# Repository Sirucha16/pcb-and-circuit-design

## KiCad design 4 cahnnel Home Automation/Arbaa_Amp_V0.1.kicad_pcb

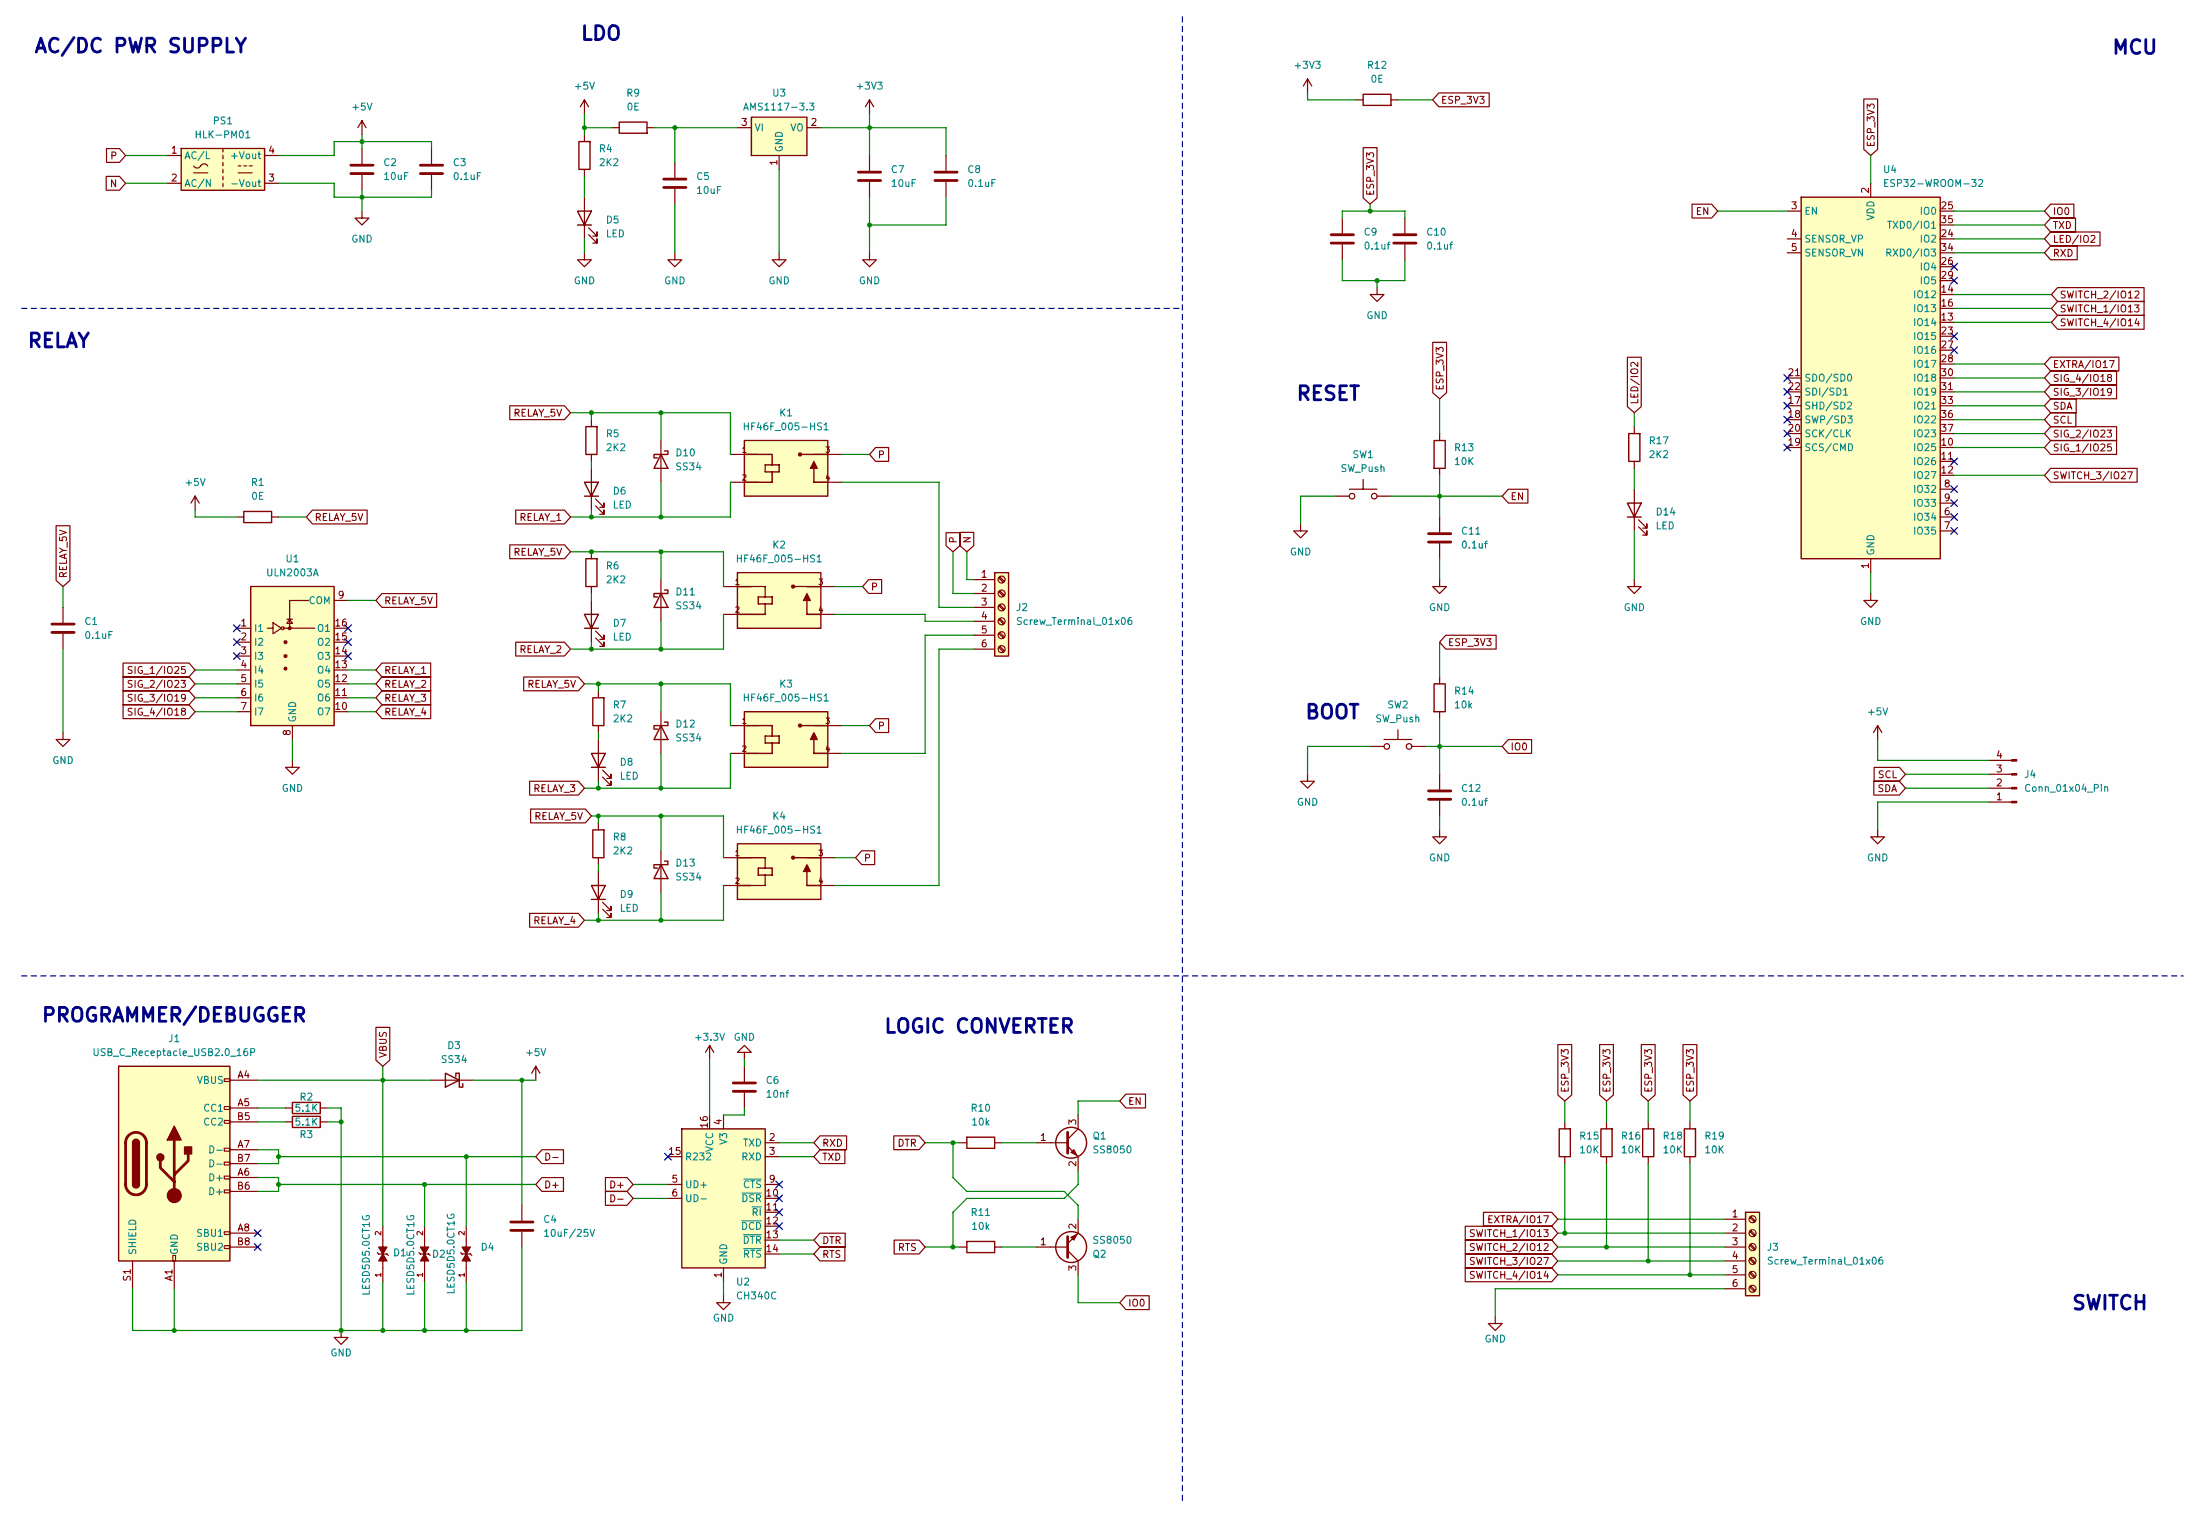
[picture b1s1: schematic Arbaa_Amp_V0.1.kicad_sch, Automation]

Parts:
C1, C3, C8: 0.1uF; C_0603_1608Metric
C2, C5, C7: 10uF; C_1206_3216Metric
C4: 10uF/25V; C_0603_1608Metric
C6: 10nf; C_1206_3216Metric
C9, C10, C11, C12: 0.1uf; C_0603_1608Metric
D1, D2, D4: LESD5D5.0CT1G; TVS_LESD5D5.0CT1G; PARTREV O
D3, D10, D11, D12, D13: SS34; D_SMA
D5, D6, D7, D8, D9, D14: LED; LED_0603_1608Metric
J1: USB_C_Receptacle_USB2.0_16P; USB_C_Receptacle_HCTL_HC-TYPE-C-16P-01A
J2, J3: Screw_Terminal_01x06; TerminalBlock_bornier-6_P5.08mm
J4: Conn_01x04_Pin; PinHeader_1x04_P2.54mm_Vertical
K1, K2, K3, K4: HF46F_005-HS1; RELAY_HF46F_005-HS1; PARTREV 1.00
PS1: HLK-PM01; Converter_ACDC_Hi-Link_HLK-PMxx
Q1, Q2: SS8050; SOT-23
R1, R9, R12: 0E; R_0603_1608Metric
R2, R3: 5.1K; R_0603_1608Metric
R4, R5, R6, R7, R8, R17: 2K2; R_0603_1608Metric
R10, R11, R14: 10k; R_0603_1608Metric
R13, R15, R16, R18, R19: 10K; R_0603_1608Metric
SW1, SW2: SW_Push; SW_Push_SPST_NO_Alps_SKRK
U1: ULN2003A; SOIC-16_3.9x9.9mm_P1.27mm
U2: CH340C; SOIC-16_3.9x9.9mm_P1.27mm
U3: AMS1117-3.3; SOT-223-3_TabPin2
U4: ESP32-WROOM-32

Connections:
+3.3V: U2.16 (VCC)
+3V3: C7.1, C8.1, R12.1, U3.2 (VO)
+5V: C2.1, C3.1, C4.1, D3.1 (K), J4.4, PS1.4 (+Vout), R1.1, R4.2, R9.1
D+: D2.2, J1.A6 (D+), J1.B6 (D+), U2.5 (UD+)
D-: D4.2, J1.A7 (D-), J1.B7 (D-), U2.6 (UD-)
DTR: Q2.2 (E), R10.2, U2.13 (~DTR)
EN: C11.1, Q1.3 (C), R13.2, SW1.2, U4.3 (EN)
ESP_3V3: C9.1, C10.1, R12.2, R13.1, R14.1, R15.2, R16.2, R18.2, R19.2, U4.2 (VDD)
EXTRA/IO17: J3.1, U4.28 (IO17)
GND: C1.2, C2.2, C3.2, C4.2, C5.2, C6.1, C7.2, C8.2, C9.2, C10.2, C11.2, C12.2, D1.1, D2.1, D4.1, D5.1 (K), D14.1 (K), J1.A1 (GND), J1.A12 (GND), J1.B1 (GND), J1.B12 (GND), J1.S1 (SHIELD), J3.6, J4.1, PS1.3 (-Vout), R2.2, R3.2, SW1.1, SW2.1, U1.8 (GND), U2.1 (GND), U3.1 (GND), U4.1 (GND), U4.15 (GND), U4.38 (GND), U4.39 (GND)
IO0: C12.1, Q2.3 (C), R14.2, SW2.2, U4.25 (IO0)
LED/IO2: R17.2, U4.24 (IO2)
N: J2.1, PS1.2 (AC/N)
unnamed: D5.2 (A), R4.1
unnamed: D6.2 (A), R5.1
unnamed: D7.2 (A), R6.1
unnamed: D8.2 (A), R7.1
unnamed: D9.2 (A), R8.1
unnamed: D14.2 (A), R17.1
unnamed: J1.A5 (CC1), R2.1
unnamed: J1.B5 (CC2), R3.1
unnamed: J2.3, K1.4
unnamed: J2.4, K2.4
unnamed: J2.5, K3.4
unnamed: J2.6, K4.4
unnamed: Q1.1 (B), R10.1
unnamed: Q2.1 (B), R11.1
unnamed: C6.2, U2.4 (V3)
unnamed: C5.1, R9.2, U3.3 (VI)
P: J2.2, K1.3, K2.3, K3.3, K4.3, PS1.1 (AC/L)
RELAY_1: D6.1 (K), D10.2 (A), K1.2, U1.13 (O4)
RELAY_2: D7.1 (K), D11.2 (A), K2.2, U1.12 (O5)
RELAY_3: D8.1 (K), D12.2 (A), K3.2, U1.11 (O6)
RELAY_4: D9.1 (K), D13.2 (A), K4.2, U1.10 (O7)
RELAY_5V: C1.1, D10.1 (K), D11.1 (K), D12.1 (K), D13.1 (K), K1.1, K2.1, K3.1, K4.1, R1.2, R5.2, R6.2, R7.2, R8.2, U1.9 (COM)
RTS: Q1.2 (E), R11.2, U2.14 (~RTS)
RXD: U2.2 (TXD), U4.34 (RXD0/IO3)
SCL: J4.3, U4.36 (IO22)
SDA: J4.2, U4.33 (IO21)
SIG_1/IO25: U1.4 (I4), U4.10 (IO25)
SIG_2/IO23: U1.5 (I5), U4.37 (IO23)
SIG_3/IO19: U1.6 (I6), U4.31 (IO19)
SIG_4/IO18: U1.7 (I7), U4.30 (IO18)
SWITCH_1/IO13: J3.2, R15.1, U4.16 (IO13)
SWITCH_2/IO12: J3.3, R16.1, U4.14 (IO12)
SWITCH_3/IO27: J3.4, R18.1, U4.12 (IO27)
SWITCH_4/IO14: J3.5, R19.1, U4.13 (IO14)
TXD: U2.3 (RXD), U4.35 (TXD0/IO1)
VBUS: D1.2, D3.2 (A), J1.A4 (VBUS), J1.A9 (VBUS), J1.B4 (VBUS), J1.B9 (VBUS)

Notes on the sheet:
SWITCH
MCU
PROGRAMMER/DEBUGGER
LOGIC CONVERTER
RESET
BOOT
LDO
RELAY
AC/DC PWR SUPPLY

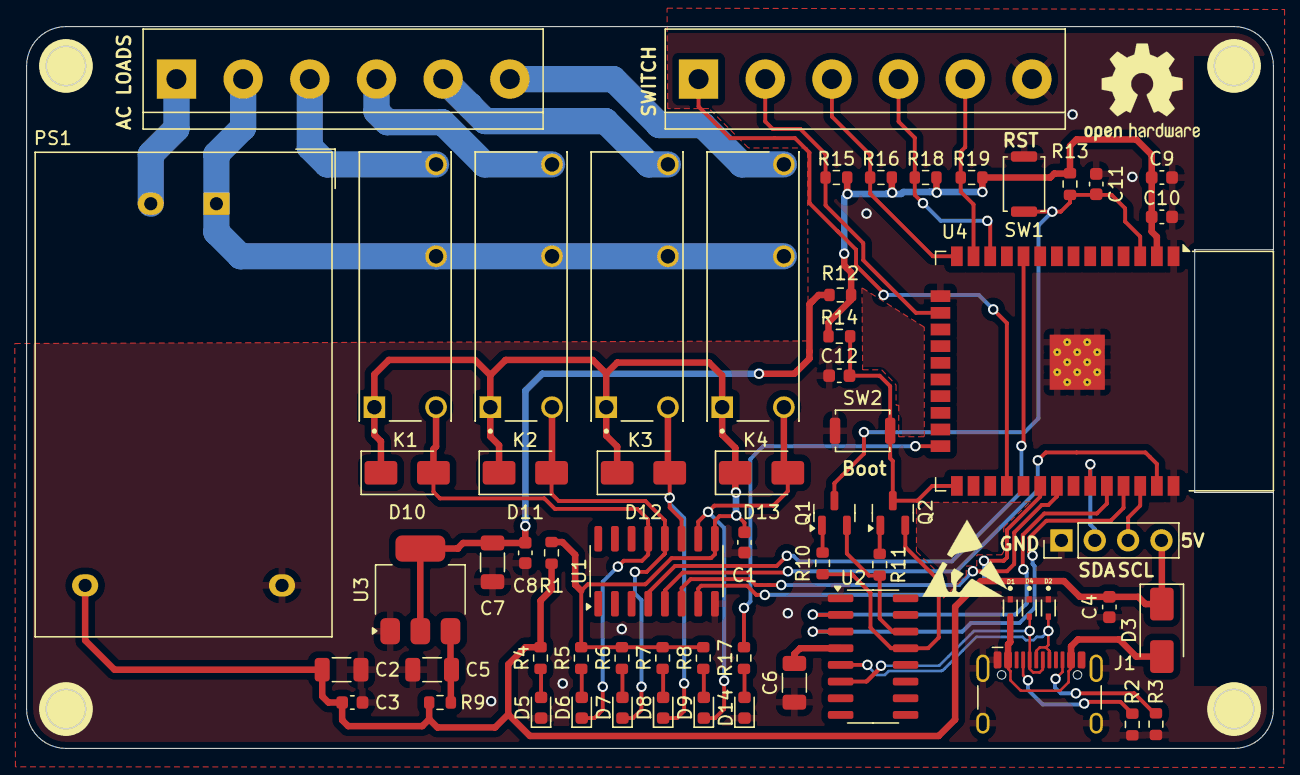
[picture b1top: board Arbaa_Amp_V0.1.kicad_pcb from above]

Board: 2 copper layers, 95.0 x 55.0 mm, 62 parts (0 on the bottom side), 48 nets.

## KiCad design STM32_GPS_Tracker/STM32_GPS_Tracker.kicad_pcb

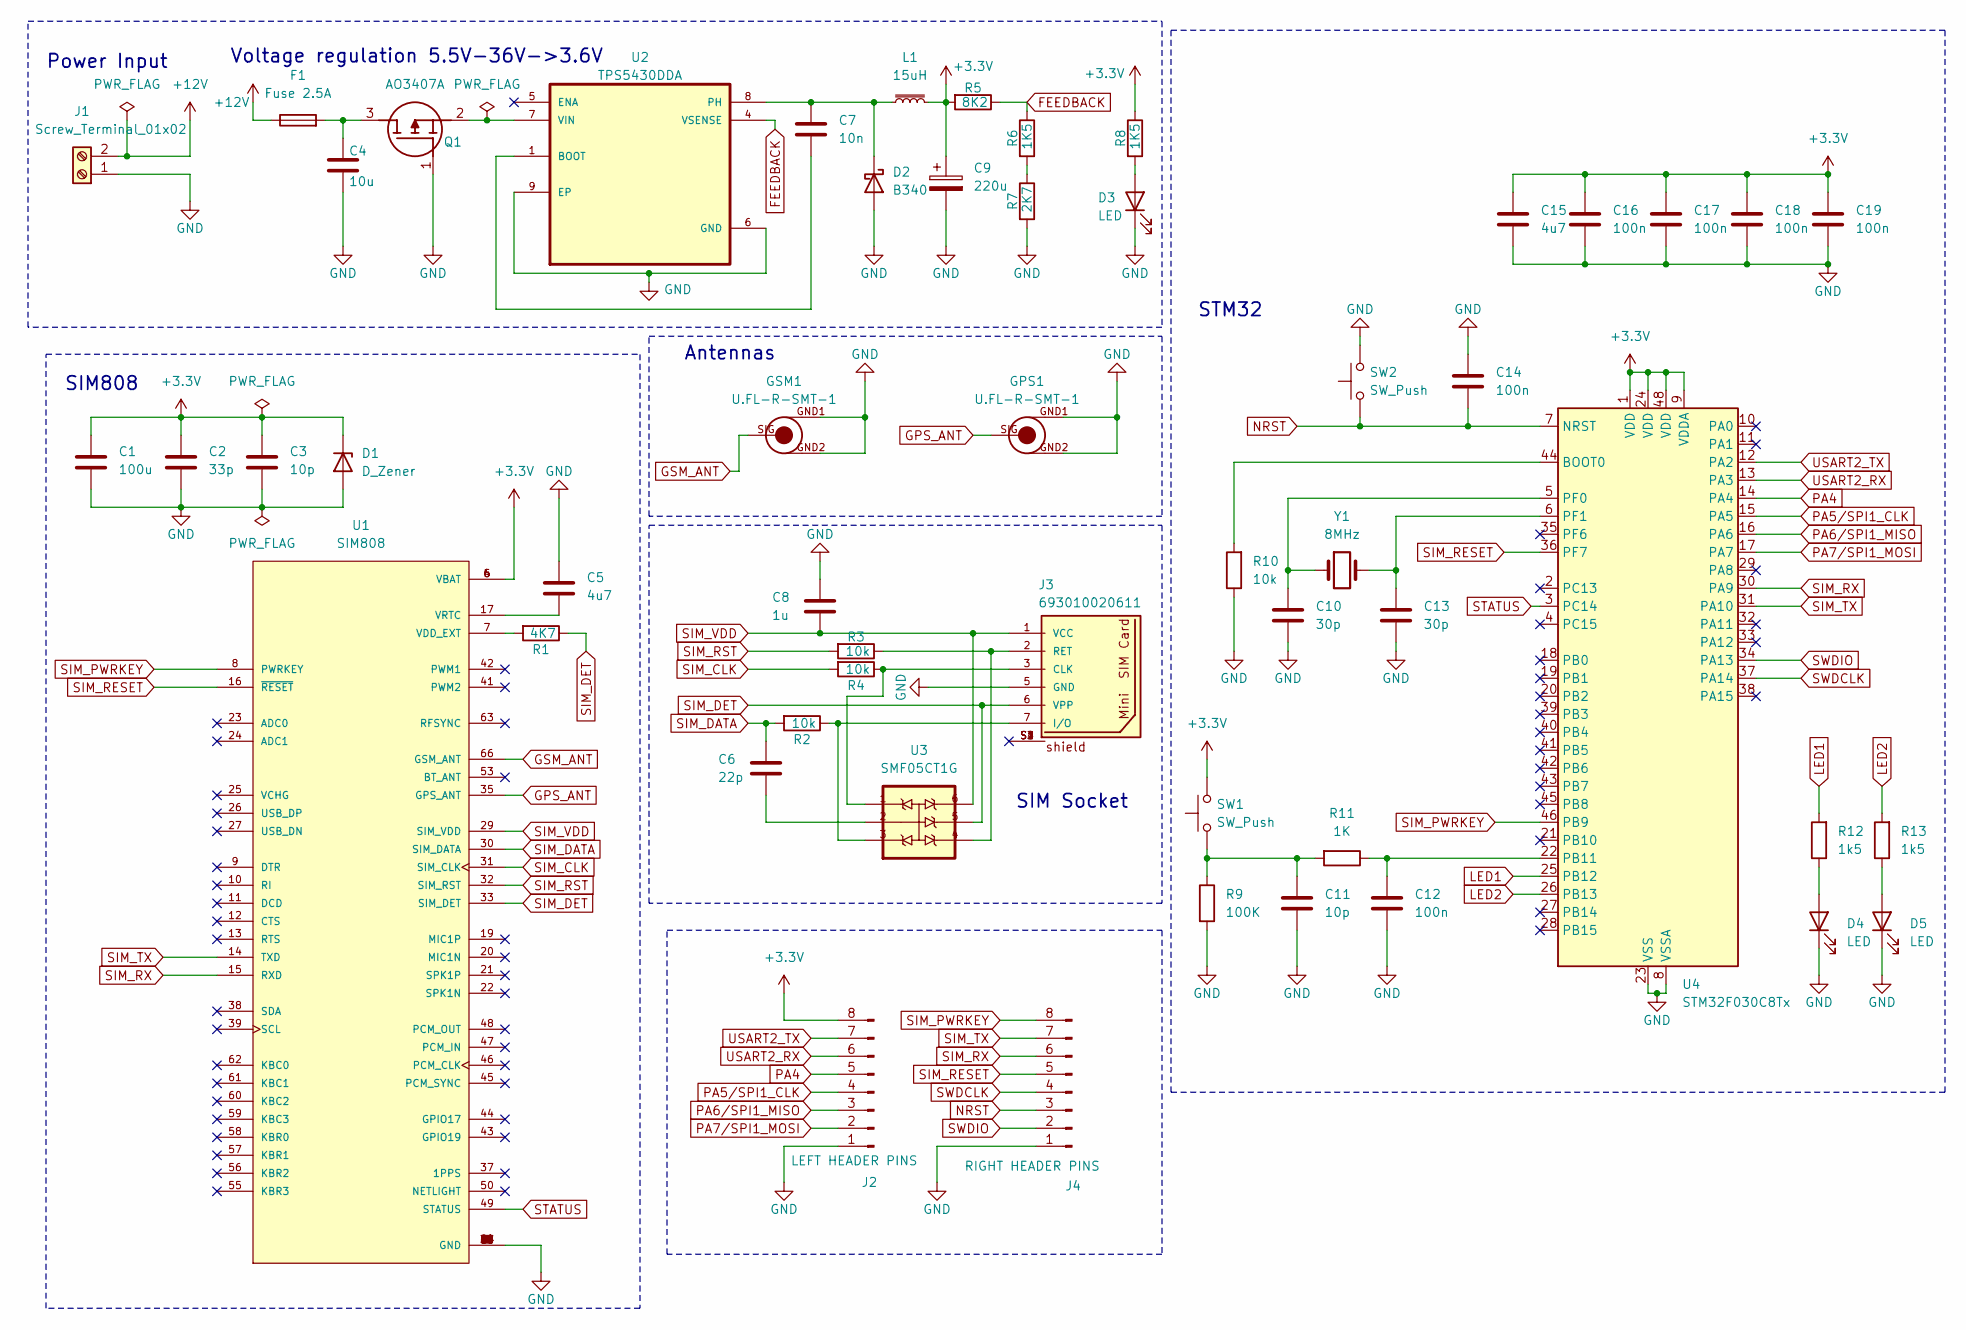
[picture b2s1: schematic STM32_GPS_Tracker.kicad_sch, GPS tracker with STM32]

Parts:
C1: 100u; C_1206_3216Metric
C2: 33p; C_0402_1005Metric
C3, C11: 10p; C_0402_1005Metric
C4: 10u; C_0805_2012Metric
C5, C15: 4u7; C_0201_0603Metric
C6: 22p; C_0402_1005Metric
C7: 10n; C_0201_0603Metric
C8: 1u; C_0402_1005Metric
C9: 220u; CP_EIA-7343-15_Kemet-W
C10, C13: 30p; C_0402_1005Metric
C12, C14, C16, C17, C18, C19: 100n; C_0402_1005Metric
D1: D_Zener; D_0805_2012Metric
D2: B340; D_SMC
D3, D4, D5: LED; LED_0603_1608Metric
F1: Fuse 2.5A; Fuse_0402_1005Metric
GPS1: U.FL-R-SMT-1
GSM1: U.FL-R-SMT-1
J1: Screw_Terminal_01x02; TerminalBlock_Phoenix_MKDS-1,5-2_1x02_P5.00mm_Horizontal
J2: LEFT HEADER PINS; PinHeader_1x08_P2.54mm_Vertical
J3: 693010020611; PART-NUMBER 693010020611
J4: RIGHT HEADER PINS; PinHeader_1x08_P2.54mm_Vertical
L1: 15uH; L_10.4x10.4_H4.8
Q1: AO3407A; SOT95P280X125-3N; Manufacturer_Part_Number AO3407A
R1: 4K7; R_0402_1005Metric
R2, R3, R4, R10: 10k; R_0402_1005Metric
R5: 8K2; R_0805_2012Metric
R6, R8: 1K5; R_0805_2012Metric
R7: 2K7; R_0805_2012Metric
R9: 100K; R_0201_0603Metric
R11: 1K; R_0603_1608Metric
R12, R13: 1k5; R_0805_2012Metric
SW1, SW2: SW_Push; SW_Push_1P1T_NO_CK_KSC7xxJ
U1: SIM808; XCVR_SIM808; PARTREV 1.03
U2: TPS5430DDA; VREG_LM5017MR_NOPB
U3: SMF05CT1G; SOT65P210X110-6N
U4: STM32F030C8Tx; LQFP-48_7x7mm_P0.5mm
Y1: 8MHz; Crystal_SMD_5032-2Pin_5.0x3.2mm

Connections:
+3.3V: C1.1, C2.1, C3.1, C9.1, C15.1, C16.1, C17.1, C18.1, C19.1, D1.1 (K), J2.8, L1.2, R5.2, R8.1, SW1.2, U1.4 (VBAT), U1.5 (VBAT), U1.6 (VBAT), U4.1 (VDD), U4.9 (VDDA), U4.24 (VDD), U4.48 (VDD); also elsewhere on the board
+12V: F1.1, J1.2
FEEDBACK: R5.1, R6.1, U2.4 (VSENSE)
GND: C1.2, C2.2, C3.2, C4.2, C5.1, C8.1, C9.2, C10.2, C11.2, C12.2, C13.2, C14.1, C15.2, C16.2, C17.2, C18.2, C19.2, D1.2 (A), D2.2 (A), D3.1 (K), D4.1 (K), D5.1 (K), GPS1.GND1, GPS1.GND2, GSM1.GND1, GSM1.GND2, J1.1, J2.1, J3.5 (GND), J4.1, Q1.1 (G), R7.2, R9.2, R10.1, SW2.2, U1.1 (GND), U1.2 (GND), U1.3 (GND), U1.18 (GND), U1.28 (GND), U1.34 (GND), U1.36 (GND), U1.40 (GND), U1.51 (GND), U1.52 (GND), U1.54 (GND), U1.64 (GND), U1.65 (GND), U1.67 (GND), U1.68 (GND), U2.6 (GND), U2.9 (EP), U4.8 (VSSA), U4.23 (VSS), U4.47 (VSS); also elsewhere on the board
GPS_ANT: GPS1.SIG, U1.35 (GPS_ANT)
GSM_ANT: GSM1.SIG, U1.66 (GSM_ANT)
LED1: R12.2, U4.25 (PB12)
LED2: R13.2, U4.26 (PB13)
NRST: C14.2, J4.3, SW2.1, U4.7 (NRST); also elsewhere on the board
unnamed: C6.2, U3.2
unnamed 10: C11.1, R9.1, R11.2, SW1.1; also elsewhere on the board
unnamed: C7.2, D2.1 (K), L1.1, U2.8 (PH)
unnamed: D3.2 (A), R8.2
unnamed: D4.2 (A), R12.1
unnamed: D5.2 (A), R13.1
unnamed: J3.3 (CLK), R4.1, U3.1
unnamed: J3.7 (I/O), R2.1, U3.3
unnamed: J3.2 (RET), R3.1, U3.4
unnamed: C4.1, F1.2, Q1.3 (D)
unnamed: Q1.2 (S), U2.7 (VIN)
unnamed: R6.2, R7.1
unnamed: R1.2, U1.7 (VDD_EXT)
unnamed: C5.2, U1.17 (VRTC)
unnamed: C7.1, U2.1 (BOOT)
unnamed: R10.2, U4.44 (BOOT0)
unnamed: C12.1, R11.1, U4.22 (PB11)
unnamed: C10.1, U4.5 (PF0), Y1.1
unnamed: C13.1, U4.6 (PF1), Y1.2
PA4: J2.5, U4.14 (PA4)
PA5/SPI1_CLK: J2.4, U4.15 (PA5)
PA6/SPI1_MISO: J2.3, U4.16 (PA6)
PA7/SPI1_MOSI: J2.2, U4.17 (PA7)
SIM_CLK: R4.2, U1.31 (SIM_CLK)
SIM_DATA: C6.1, R2.2, U1.30 (SIM_DATA)
SIM_DET: J3.6 (VPP), R1.1, U1.33 (SIM_DET), U3.5
SIM_PWRKEY: J4.8, U1.8 (PWRKEY), U4.46 (PB9)
SIM_RESET: J4.5, U1.16 (~RESET), U4.36 (PF7)
SIM_RST: R3.2, U1.32 (SIM_RST)
SIM_RX: J4.6, U1.15 (RXD), U4.30 (PA9)
SIM_TX: J4.7, U1.14 (TXD), U4.31 (PA10)
SIM_VDD: C8.2, J3.1 (VCC), U1.29 (SIM_VDD), U3.6
STATUS: U1.49 (STATUS), U4.3 (PC14)
SWDCLK: J4.4, U4.37 (PA14)
SWDIO: J4.2, U4.34 (PA13)
USART2_RX: J2.6, U4.13 (PA3)
USART2_TX: J2.7, U4.12 (PA2)

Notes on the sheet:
SIM Socket
Power Input
Voltage regulation 5.5V-36V->3.6V
STM32
Antennas
SIM808

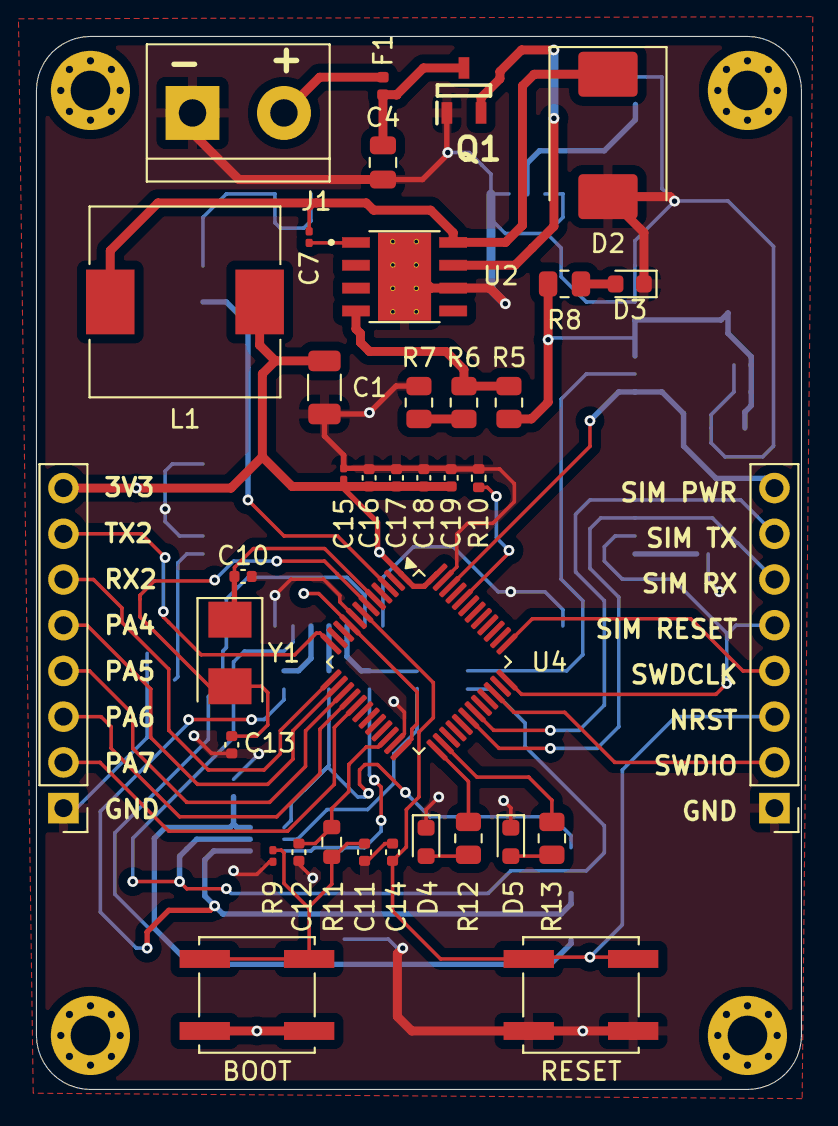
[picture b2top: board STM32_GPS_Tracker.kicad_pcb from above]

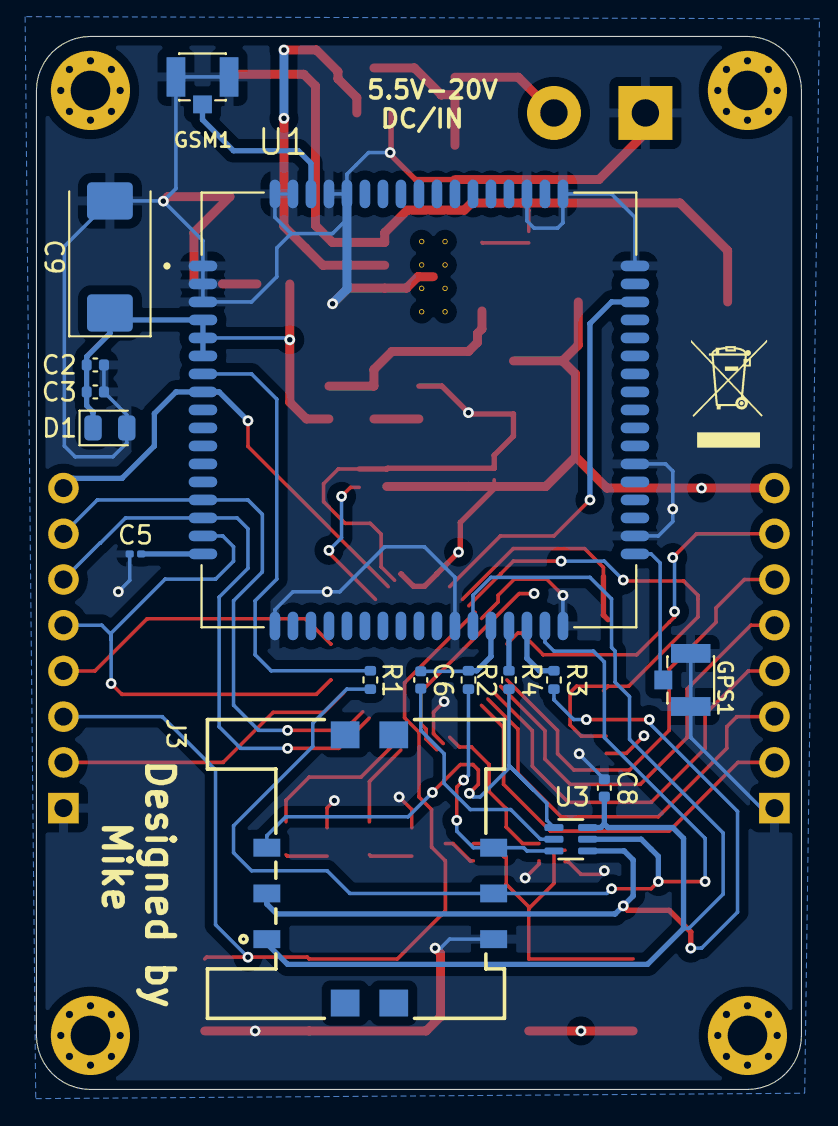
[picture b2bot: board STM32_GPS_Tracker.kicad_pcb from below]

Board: 4 copper layers, 42.5 x 58.5 mm, 57 parts (16 on the bottom side), 46 nets.

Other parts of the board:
BOOT: SW_Push; SW_Push_1P1T_NO_CK_KSC6xxJ
H1, H2, H3, H4: MountingHole_Pad; MountingHole_2.2mm_M2_Pad_Via
RESET: SW_Push; SW_Push_1P1T_NO_CK_KSC6xxJ

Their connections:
+3.3V: BOOT.2; also elsewhere on the board
GND: RESET.2; also elsewhere on the board
NRST: RESET.1; also elsewhere on the board
unnamed 10: BOOT.1; also elsewhere on the board
